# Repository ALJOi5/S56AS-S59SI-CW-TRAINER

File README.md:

# S56AS-S59SI-CW-TRAINER
---
S56AS S59SI CW TRAINER is a tool used for training your CW skills
### PCB files boda dadani Soon™
---
Ana slikca
---

---
Designed in Cerkno

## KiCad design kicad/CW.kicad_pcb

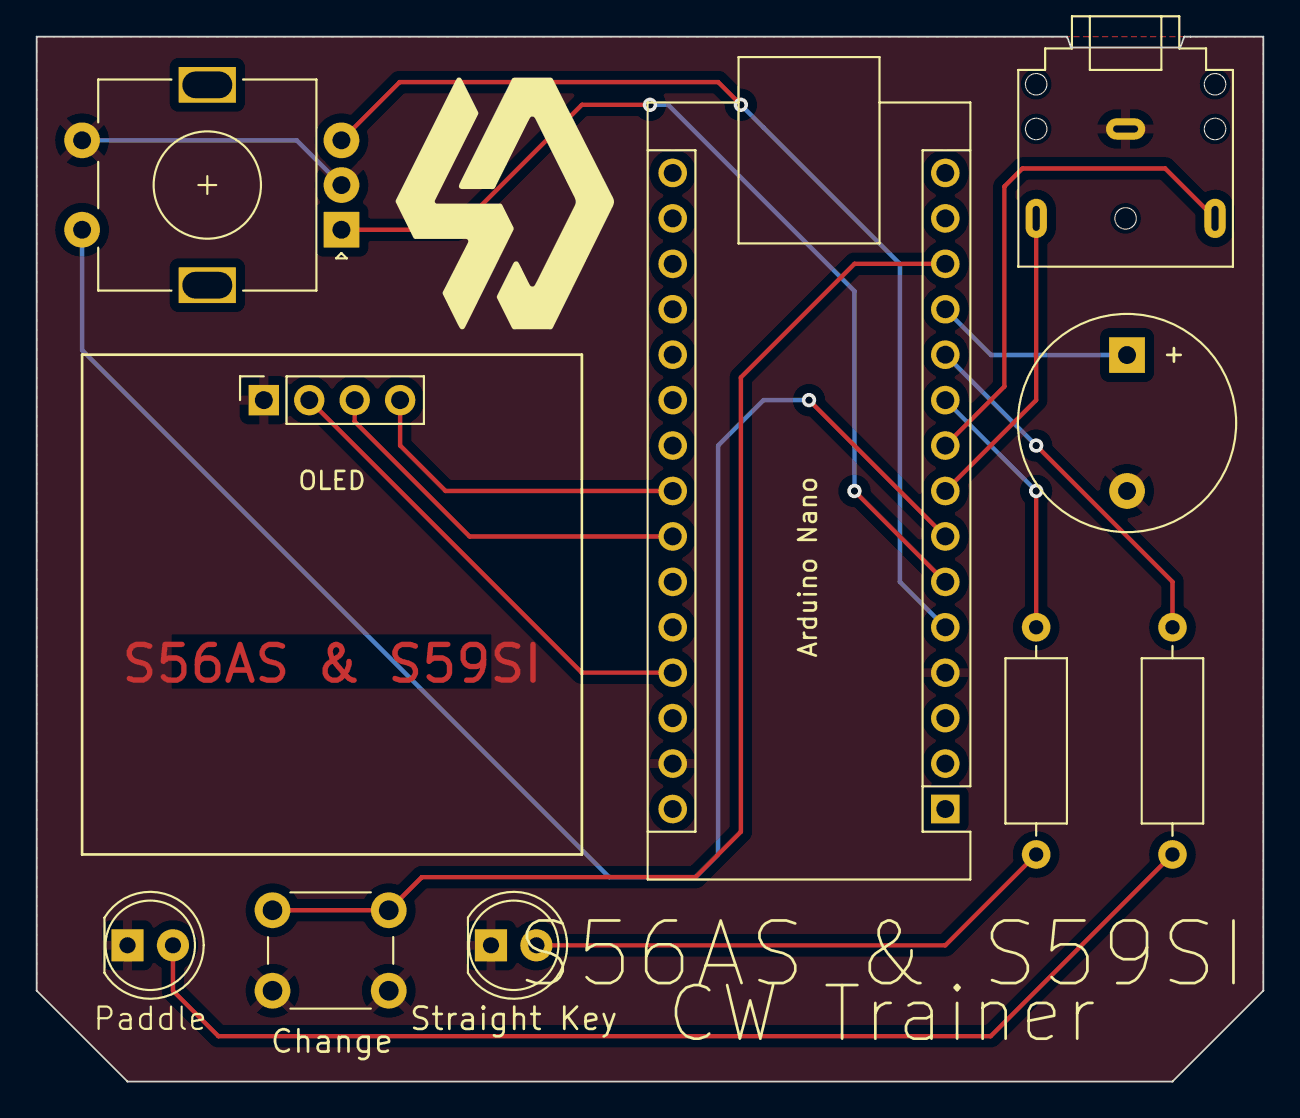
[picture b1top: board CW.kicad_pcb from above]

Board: 2 copper layers, 68.6 x 58.4 mm, 10 parts (0 on the bottom side), 12 nets.

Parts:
A1: Arduino_Nano_Every; Arduino_Nano
BZ1: Buzzer; Buzzer_12x9.5RM7.6
D1, D2: LED; LED_D5.0mm
J1: OLED; PinSocket_1x04_P2.54mm_Vertical
J2: SJ1-3523N; Jack_3.5mm_CUI_SJ1-3523N_Horizontal
J3: rotary encoder; RotaryEncoder_Alps_EC11E-Switch_Vertical_H20mm
R1, R2: 220; R_Axial_DIN0309_L9.0mm_D3.2mm_P12.70mm_Horizontal
SW1: SW_Push; SW_PUSH_6mm

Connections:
unnamed: A1.5 (D2), J3.B
unnamed: A1.6 (D3), J3.A
unnamed: A1.7 (D4), J3.S2
unnamed: A1.8 (D5), J2.T
unnamed: A1.9 (D6), J2.R
unnamed: A1.10 (D7), R1.2
unnamed: A1.11 (D8), R2.2
unnamed: A1.12 (D9), BZ1.1 (-)
unnamed: A1.13 (D10), SW1.1
unnamed: A1.4 (GND), A1.29 (GND), BZ1.2 (+), D1.1 (K), D2.1 (K), J1.1, J2.S, J3.C, J3.S1, SW1.2
unnamed: D1.2 (A), R2.1
unnamed: D2.2 (A), R1.1

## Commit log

2025-04-09 Add initial project files including configuration, source code, and documentation
2025-06-25 Create lib
